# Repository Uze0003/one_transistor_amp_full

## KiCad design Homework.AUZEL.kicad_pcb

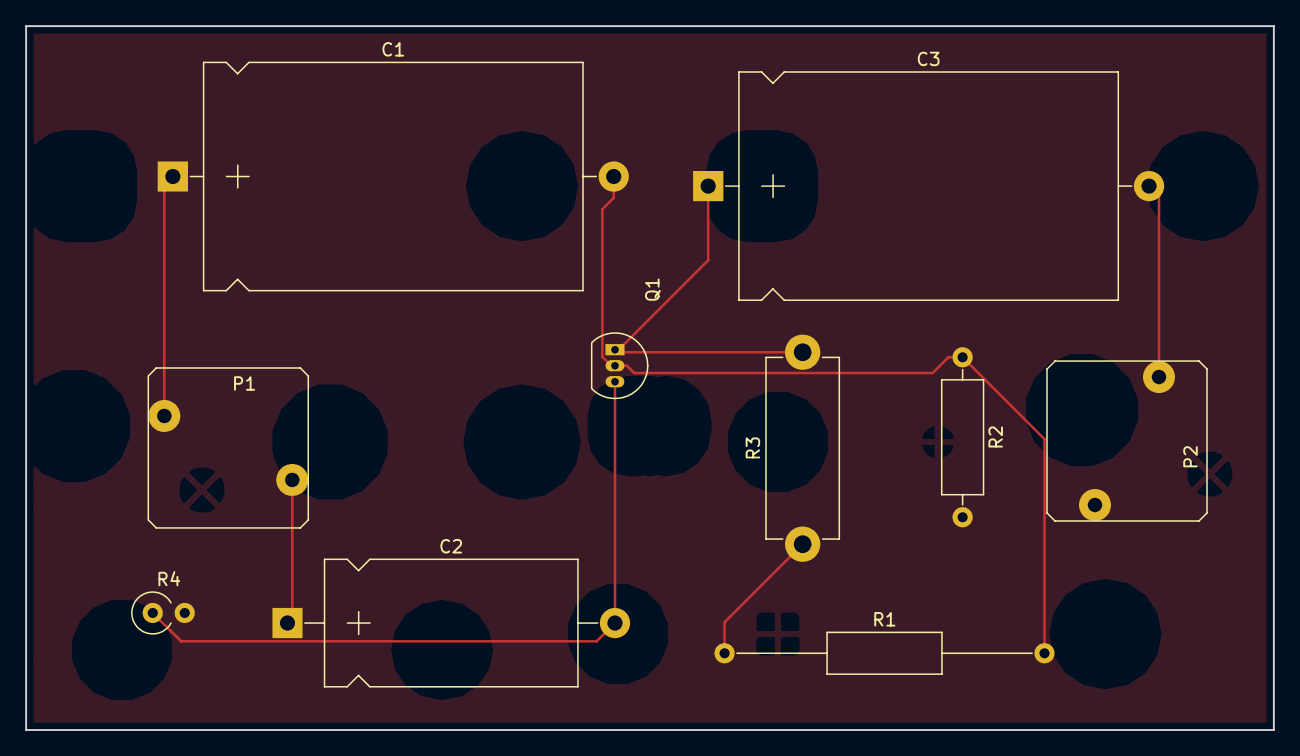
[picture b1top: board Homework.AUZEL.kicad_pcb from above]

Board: 2 copper layers, 99.1 x 55.9 mm, 10 parts (0 on the bottom side), 7 nets.

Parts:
C1, C3: 20uF; CP_Axial_L30.0mm_D18.0mm_P35.00mm_Horizontal
C2: 50uF; CP_Axial_L20.0mm_D10.0mm_P26.00mm_Horizontal
P1: SIGNAL_IN; SW_PUSH
P2: SIGNAL_OUT; SW_PUSH
Q1: BC548; TO-92_Inline_Narrow_Oval
R1: 22k; R_Axial_DIN0309_L9.0mm_D3.2mm_P25.40mm_Horizontal
R2: 6.8k; R_Axial_DIN0309_L9.0mm_D3.2mm_P12.70mm_Horizontal
R3: 4.7k; R_Axial_DIN0614_L14.3mm_D5.7mm_P15.24mm_Horizontal
R4: 1.8k; R_Axial_DIN0309_L9.0mm_D3.2mm_P2.54mm_Vertical

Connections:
+12V: R1.1, R3.1
GND: C2.1, P1.2, P2.2, R2.2, R4.2
unnamed: C1.1, P1.1
unnamed: C1.2, Q1.2, R1.2, R2.1
unnamed: C2.2, Q1.3, R4.1
unnamed: C3.1, Q1.1, R3.2
unnamed: C3.2, P2.1

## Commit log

2017-05-27 Abdurrahman_Uzel_Sıngle_Transistor_Amp_All
